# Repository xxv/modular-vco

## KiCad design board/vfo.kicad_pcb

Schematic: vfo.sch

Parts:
C1, C2: 10nF; C_0805_2012Metric_Pad1.15x1.40mm_HandSolder; MPN CC0805MKX7RYBB103
C3: 1nF; C_0805_2012Metric_Pad1.15x1.40mm_HandSolder; MPN CC0805KRX7RABB102
D1, D2: DIODE; D_0805_2012Metric_Pad1.15x1.40mm_HandSolder
J1: CVIN; Jack_3.5mm_QingPu_WQP-PJ398SM_Vertical_CircularHoles
J2: SAW; Jack_3.5mm_QingPu_WQP-PJ398SM_Vertical_CircularHoles
J3: TRI; Jack_3.5mm_QingPu_WQP-PJ398SM_Vertical_CircularHoles
J4: Conn_02x05_Odd_Even; PinHeader_2x05_P2.54mm_Vertical
J5: Conn_01x06; PinHeader_1x06_P2.54mm_Vertical
J6: Daughter_top; PinSocket_1x03_P2.54mm_Vertical
J7: Mother_top; PinHeader_1x03_P2.54mm_Vertical
J8: Daughter_bottom; PinSocket_1x03_P2.54mm_Vertical
J9: Mother_bottom; PinHeader_1x03_P2.54mm_Vertical
R1: 100K; R_0805_2012Metric_Pad1.15x1.40mm_HandSolder; MPN RC0805FR-07100KL
R2, R7: 470R; R_0805_2012Metric_Pad1.15x1.40mm_HandSolder; MPN RC0805FR-07470RL
R3: 24K; R_0805_2012Metric_Pad1.15x1.40mm_HandSolder; MPN RC0805FR-0724KL
R4: 5.6K; R_0805_2012Metric_Pad1.15x1.40mm_HandSolder; MPN RC0805FR-075K6L
R5: 1.8K; R_0805_2012Metric_Pad1.15x1.40mm_HandSolder; MPN RC0805FR-071K82L
R6: 620R; R_0805_2012Metric_Pad1.15x1.40mm_HandSolder; MPN RC0805FR-07820RL
R8: 1.5M; R_0805_2012Metric_Pad1.15x1.40mm_HandSolder; MPN RC0805FR-071M5L
R9: 100K; R_0805_2012Metric_Pad1.15x1.40mm_HandSolder
RV1: 100K; Potentiometer_Alps_RK09L_Single_Vertical
RV2: 10K; Potentiometer_Bourns_3314J_Vertical; MPN 3314J-1-103E
U1: TL072; SOIC-8_3.9x4.9mm_P1.27mm; MPN TL072CDR
U2: AS3340; DIP-16_W7.62mm_Socket; MPN AS3340

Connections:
+12V: D1.2, J7.1, R8.1, U1.8 (V+), U2.16
-12V: D2.1, J5.6, R6.2, U1.4 (V-)
/12V_IN: D1.1, J4.1, J4.2
/-12V_IN: D2.2, J4.9, J4.10
/CAP: C3.1, U2.11
/CV_IN: J7.3, R1.1
/D_12V: J6.1, RV1.1
/D_CV_IN: J1.T, J6.3
/D_GND: J1.S, J2.S, J3.S, J6.2
/D_SAW_OUT: J2.T, J8.1
/D_TRI_OUT: J3.T, J8.2
/D_TUNE_POT: J8.3, RV1.2, RV1.3
/SAW_OUT: J9.1, U1.1, U1.2 (-)
/TRI_OUT: J9.2, U1.6 (-), U1.7
/TUNE: R3.2, RV2.1
/TUNE_POT: J9.3, R9.1
/VEE_R: R4.2, R6.1, RV2.2, RV2.3, U2.3
/VFCI: R1.2, R2.2, R9.2, U2.15
/VHFT: J5.4, U2.7
/VHSI: J5.3, U2.6
/VLFI: R7.2, R8.2, U2.13
/VP: J5.1, U2.4
/VPWM: J5.2, U2.5
/VSO: U1.3 (+), U2.8
/VSSI: J5.5, U2.9
/VTO: U1.5 (+), U2.10
GND: C1.1, C2.1, C3.2, J4.3, J4.4, J4.5, J4.6, J4.7, J4.8, J7.2, R5.2, U2.12
unnamed: C1.2, R2.1
unnamed: C2.2, R7.1
unnamed: R3.1, U2.1
unnamed: R4.1, U2.2
unnamed: R5.1, U2.14

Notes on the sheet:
Output Protection
Power Bus
Disconnected Pin Breakout
CV in
Tuning
Front Panel Board

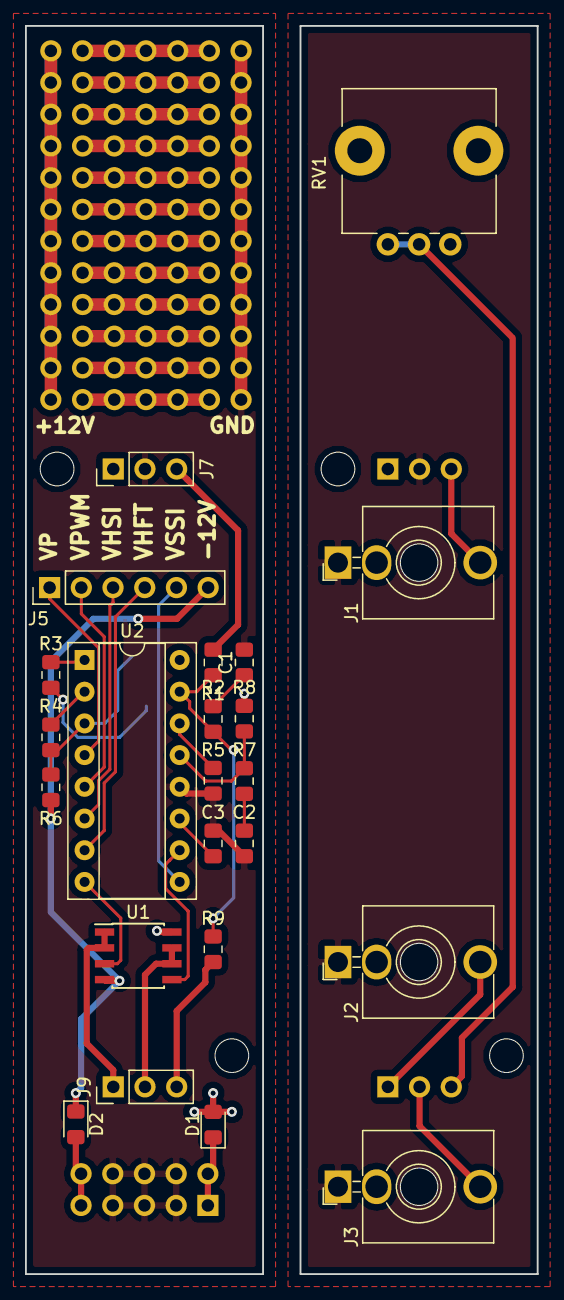
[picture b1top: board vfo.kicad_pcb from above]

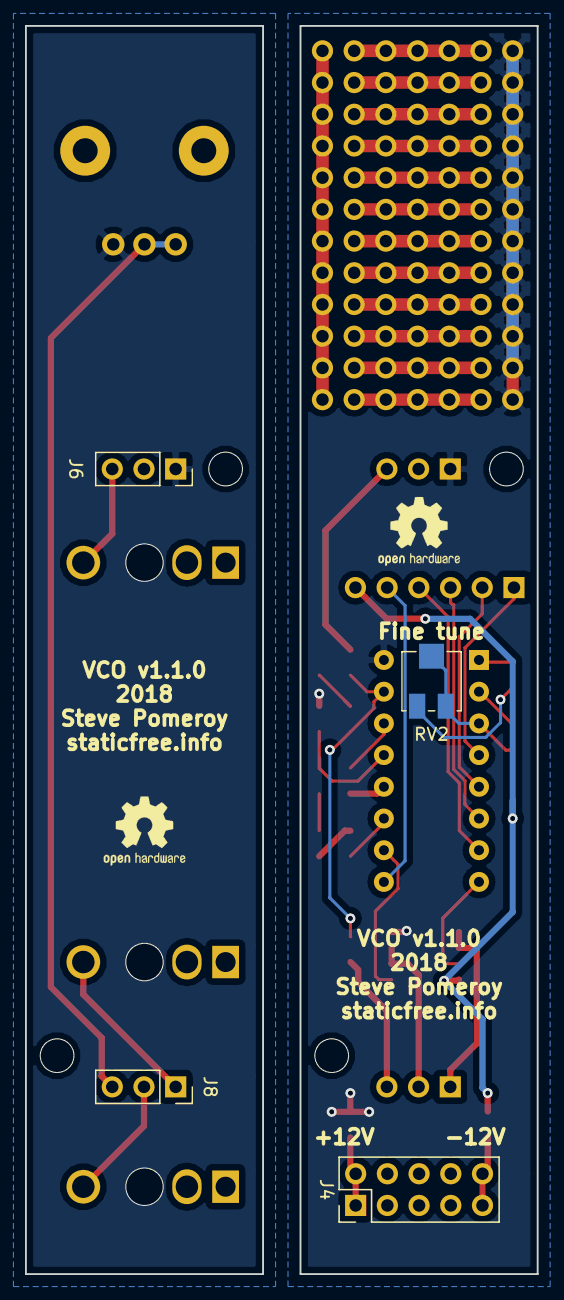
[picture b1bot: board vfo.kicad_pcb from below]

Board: 2 copper layers, 41.0 x 100.0 mm, 27 parts (4 on the bottom side), 32 nets.

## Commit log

2018-09-02 Fix 400R R2 resistor
2018-09-02 Add mounting hole measurements to Fab
2018-09-02 Update for 19mm width
2018-09-02 Reworked for 24mm wide
2018-09-02 Minor output tweaks
2018-09-02 Add BOM details
2018-09-02 Improve Fab layer
2018-09-02 Organize better
2018-09-02 First pass at faceplate
2018-09-02 Re-toggle layers
2018-09-07 Tune: widen hole to 7mm; change label
2018-09-09 Use correct resistor value
2018-09-09 Add missing 100K resistor
2018-09-09 Break into two boards
2018-09-09 Add labels
2018-09-24 Add protection diodes
